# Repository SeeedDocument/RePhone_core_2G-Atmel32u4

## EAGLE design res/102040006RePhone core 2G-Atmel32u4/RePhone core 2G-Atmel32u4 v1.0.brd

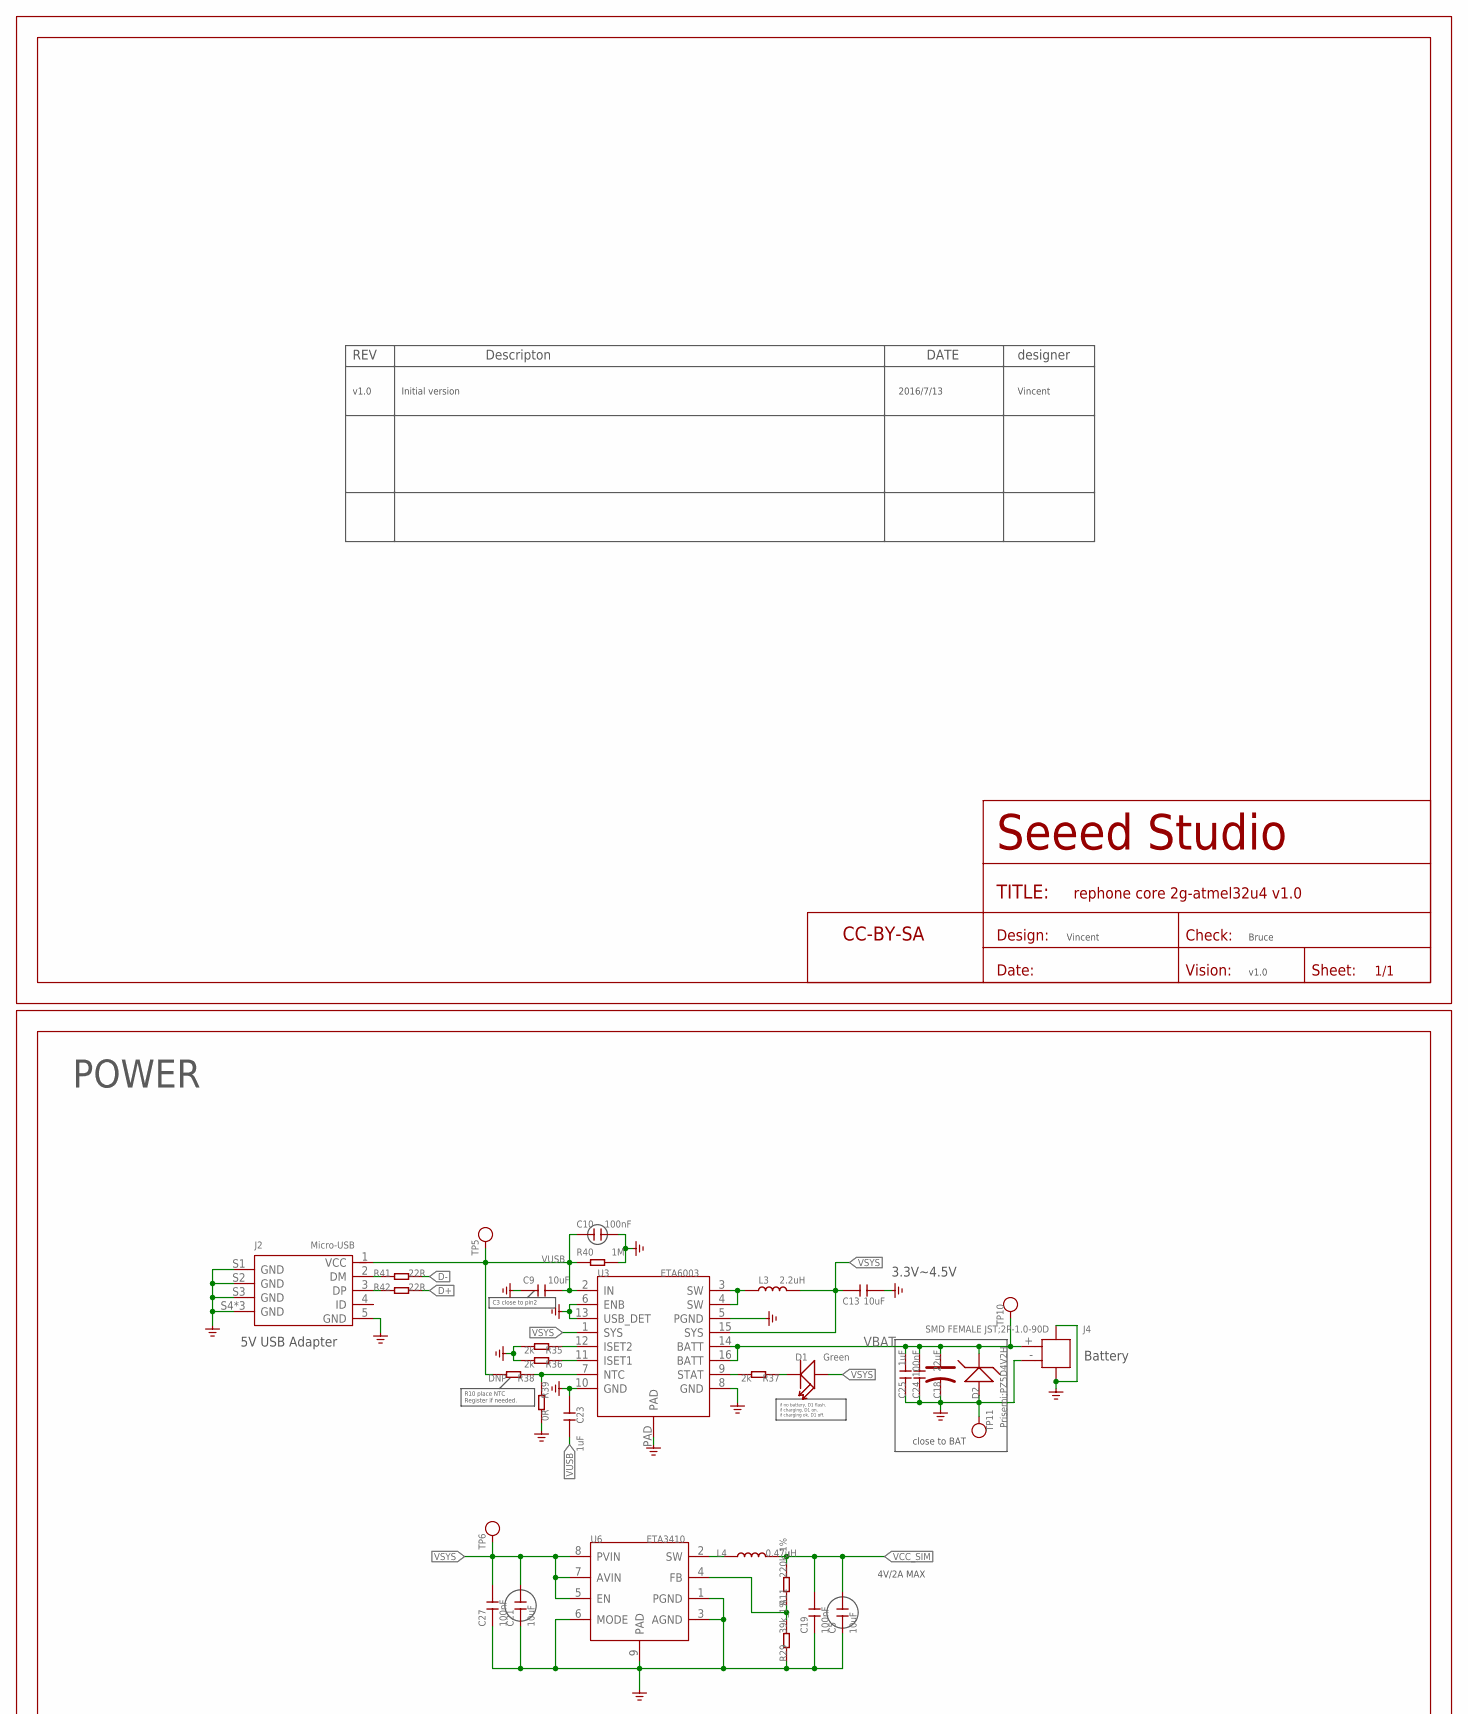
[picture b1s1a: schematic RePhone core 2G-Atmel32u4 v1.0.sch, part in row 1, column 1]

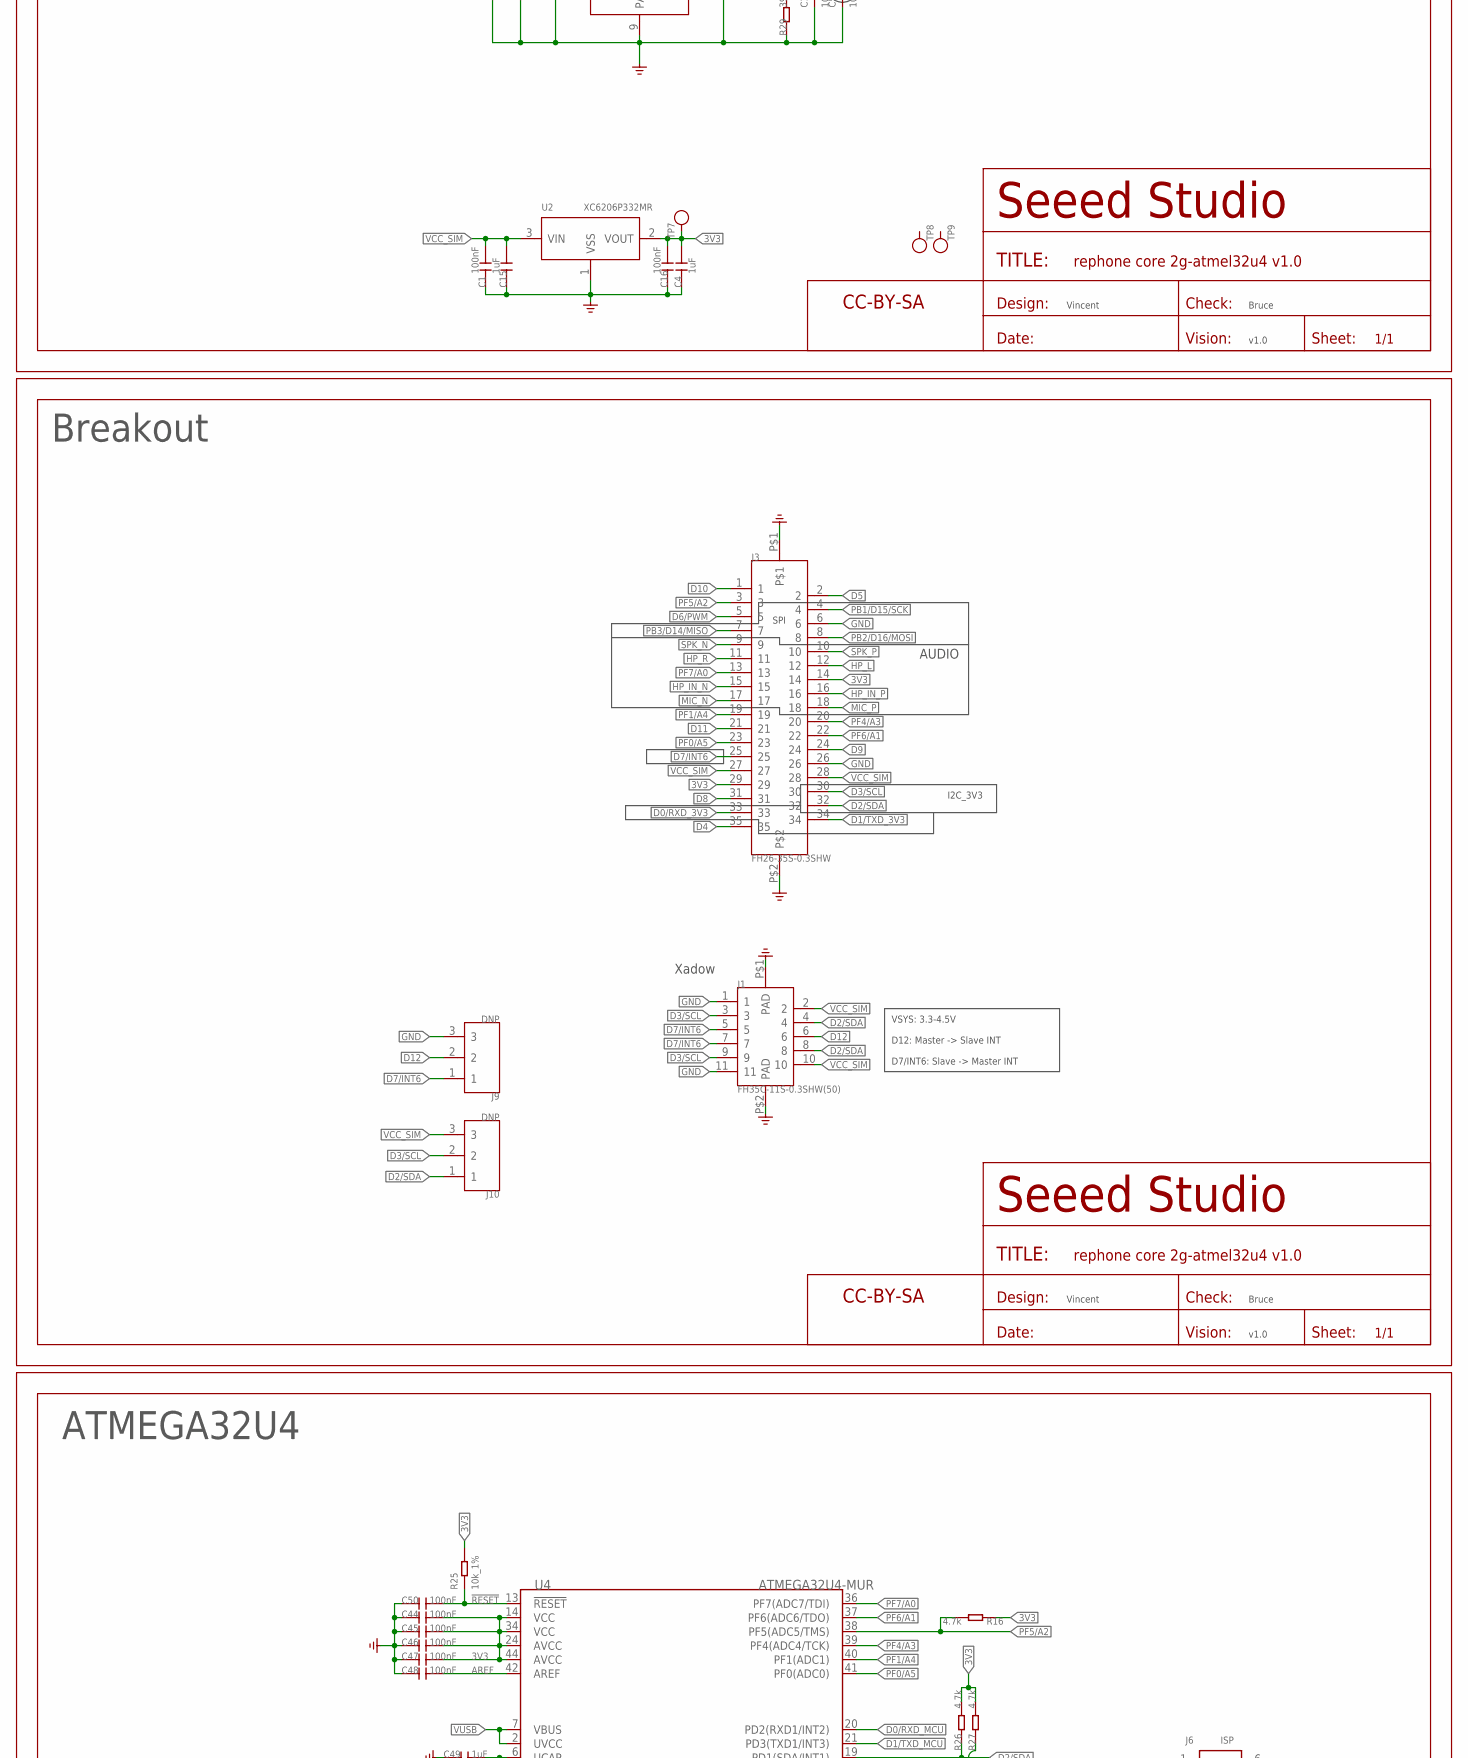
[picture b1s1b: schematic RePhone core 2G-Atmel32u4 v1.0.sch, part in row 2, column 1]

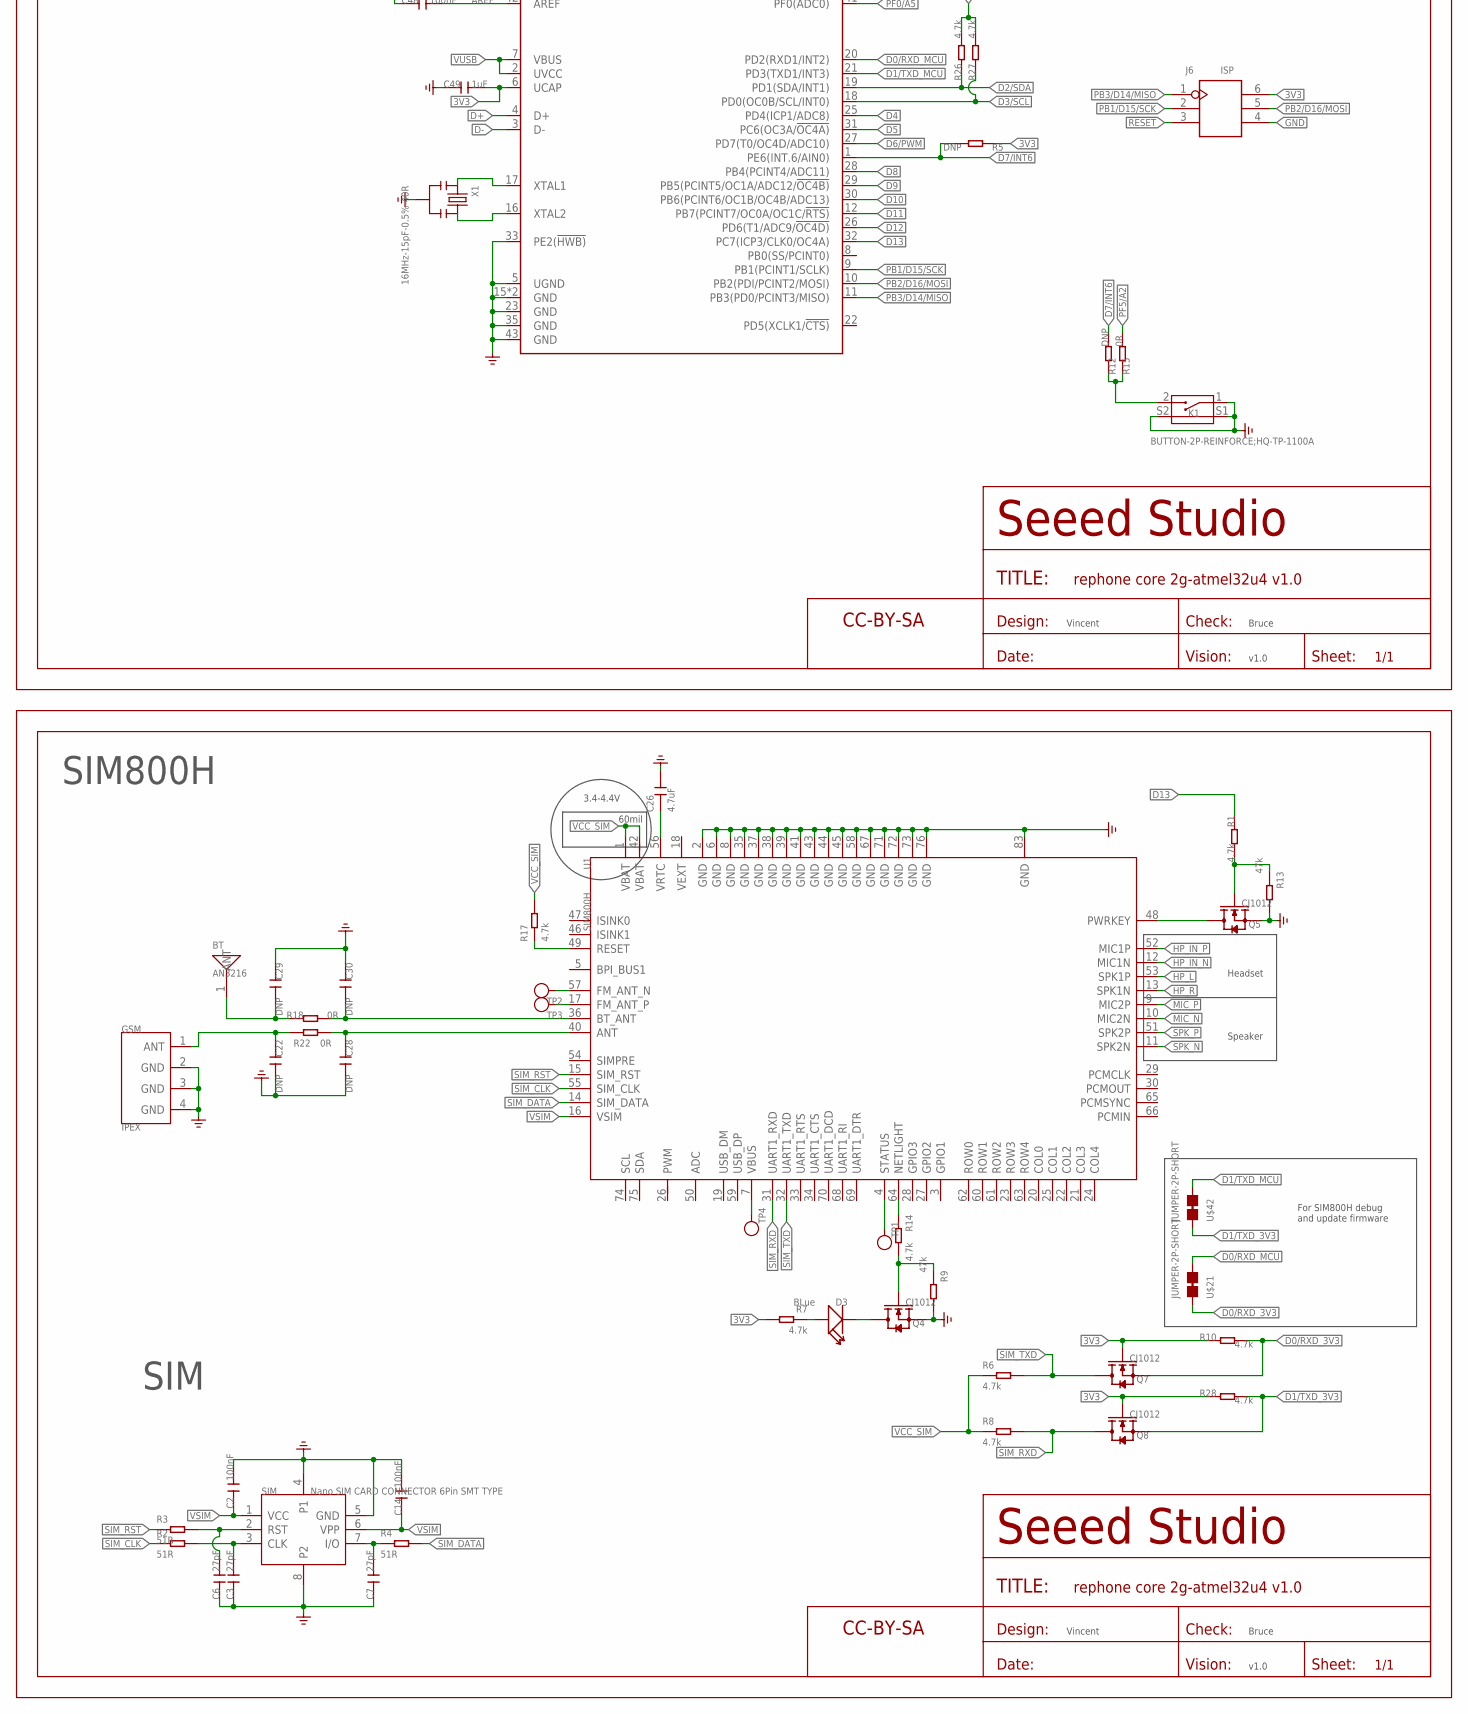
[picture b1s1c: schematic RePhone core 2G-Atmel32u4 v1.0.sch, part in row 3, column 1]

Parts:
BT: AN3216; ANT-SMD2P-3.2X1.6X1.04MM
C1, C2, C10, C14, C16, C19, C24, C27, C44, C45, C46, C47, C48, C50: 100nF; C0201
C3, C6, C7: 27pF; C0201
C4, C15, C23, C25, C49: 1uF; C0402
C5, C9, C13, C21: 10uF; C0603
C18: 22uF; AVX-A
C22, C28, C29, C30: DNP; C0201
C26: 4.7uF; C0603
D1: Green; LED-0402
D2: Prisemi;PZ5D4V2H; SOD-523
D3: BLue; LED-0402
FR1, FR2: SEEEDSTUDIO-OPEN-SCH-FRAME; SEEEDSTUDIO-PCB-FRAME
GSM: IPEX; ANT-IPEX4-1.7X1.7MM
J1: FH35C-11S-0.3SHW(50); FPC11-SMD-0.3(FH35C)
J2: Micro-USB; MICRO-USB5+4P-SMD-0.65-B
J3: FH26-35S-0.3SHW; FPC35-SMD-0.3(FH26W)
J4: SMD FEMALE JST;2P-1.0-90D; HW2-SMD-1.0-90D
J6: ISP; H2X3-SMD-2.0(1.143)
J9, J10: DNP; 3P-DIP-2
K1: BUTTON-2P-REINFORCE;HQ-TP-1100A; SW4-SMD-4.5X3.8X1.8MM-90D
L3: 2.2uH; L0805
L4: 0.47uH; L201610
Q4, Q5, Q7, Q8: CJ1012; SOT-523
R1, R6, R7, R8, R10, R14, R16, R17, R26, R27, R28: 4.7k; R0201
R2, R3, R4: 51R; R0201
R5, R12, R38: DNP; R0201
R9, R13: 47k; R0201
R11: 220k_1%; R0201
R15, R18, R22, R39: 0R; R0201
R25: 10k_1%; R0201
R29: 39k_1%; R0201
R35, R36, R37: 2k; R0201
R40: 1M; R0201
R41, R42: 22R; R0201
SIM: Nano SIM CARD CONNECTOR 6Pin SMT TYPE; NANO-SIM6+2P-SMD-12.3X10X1.5MM
TP1, TP4, TP5, TP6, TP7, TP8, TP9, TP10, TP11: TEST-POINT-23; TP-D23MIL
TP2, TP3: TEST-POINT'4545'; TP-D45MIL
U1: SIM800H; GPRS88-SMD-1.4-17.8X45.8X2.4MM
U2: XC6206P332MR; SOT-23
U3: ETA6003; QFN16GA-0.5-3X3MM
U4: ATMEGA32U4-MUR; QFN44G-0.5-7X7MM
U6: ETA3410; DFN8G-0.5-2X2MM
U$1, U$3, U$5: SEEEDSTUDIO-OPEN-SCH-FRAME; SEEEDSTUDIO-PCB-FRAME
U$21, U$42: JUMPER-2P-SHORT; 2P-SMD-SHORT
X1: 16MHz-15pF-0.5%-40R; RESONATOR3-SMD-3.6X1.3X0.8MM

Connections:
3V3: C4.2, C16.2, C44.2, C45.2, C46.2, C47.2, C49.2, J3.14, J3.29, J6.6, Q7.1 (G), Q8.1 (G), R5.1, R7.2, R10.1, R16.1, R25.2, R26.2, R27.2, R28.1, TP7.T, U2.2 (VOUT), U4.6 (UCAP), U4.14 (VCC), U4.24 (AVCC), U4.34 (VCC), U4.44 (AVCC)
!RESET: C50.2, J6.3, R25.1, U4.13 (!RESET)
AREF: C48.2, U4.42 (AREF)
D0/RXD_3V3: J3.33, Q7.2 (S), R10.2, U$21.1
D0/RXD_MCU: U4.20 (PD2(RXD1/INT2)), U$21.2
D1/TXD_3V3: J3.34, Q8.2 (S), R28.2, U$42.1
D1/TXD_MCU: U4.21 (PD3(TXD1/INT3)), U$42.2
D2/SDA: J1.4, J1.8, J3.32, J10.1, R26.1, U4.19 (PD1(SDA/INT1))
D3/SCL: J1.3, J1.9, J3.30, J10.2, R27.1, U4.18 (PD0(OC0B/SCL/INT0))
D4: J3.35, U4.25 (PD4(ICP1/ADC8))
D5: J3.2, U4.31 (PC6(OC3A/!OC4A))
D6/PWM: J3.5, U4.27 (PD7(T0/OC4D/ADC10))
D7/INT6: J1.5, J1.7, J3.25, J9.1, R5.2, R12.2, U4.1 (PE6(INT.6/AIN0))
D8: J3.31, U4.28 (PB4(PCINT4/ADC11))
D9: J3.24, U4.29 (PB5(PCINT5/OC1A/ADC12/!OC4B))
D10: J3.1, U4.30 (PB6(PCINT6/OC1B/OC4B/ADC13))
D11: J3.21, U4.12 (PB7(PCINT7/OC0A/OC1C/!RTS))
D12: J1.6, J9.2, U4.26 (PD6(T1/ADC9/!OC4D))
D13: R1.1, U4.32 (PC7(ICP3/CLK0/OC4A))
D+: R42.2, U4.4 (D+)
D-: R41.2, U4.3 (D-)
GND: C1.1, C2.2, C3.1, C4.1, C5.1, C6.1, C7.1, C9.2, C10.2, C13.2, C14.2, C15.1, C16.1, C18.-, C19.1, C21.1, C22.2, C23.2, C24.2, C25.2, C26.2, C27.1, C28.2, C29.1, C30.1, C44.1, C45.1, C46.1, C47.1, C48.1, C49.1, C50.1, D2.+, GSM.2 (GND), GSM.3 (GND), GSM.4 (GND), J1.1, J1.11, J1.P$1 (PAD), J1.P$2 (PAD), J2.5 (GND), J2.S1 (GND), J2.S2 (GND), J2.S3 (GND), J2.S4 (GND), J2.S5 (GND), J2.S6 (GND), J3.6, J3.26, J3.P$1, J3.P$2, J4.3, J4.4, J4.- (2), J6.4, J9.3, K1.1, K1.S1, K1.S2, Q4.2 (S), Q5.2 (S), R9.2, R13.2, R29.1, R35.2, R36.2, R39.2, R40.2, SIM.4 (P1), SIM.5 (GND), SIM.8 (P2), TP11.T, U1.2 (GND), U1.6 (GND), U1.8 (GND), U1.35 (GND), U1.37 (GND), U1.38 (GND), U1.39 (GND), U1.41 (GND), U1.43 (GND), U1.44 (GND), U1.45 (GND), U1.58 (GND), U1.67 (GND), U1.71 (GND), U1.72 (GND), U1.73 (GND), U1.76 (GND), U1.83 (GND), U2.1 (VSS), U3.5 (PGND), U3.6 (ENB), U3.8 (GND), U3.10 (GND), U3.13 (USB_DET), U3.PAD, U4.5 (UGND), U4.15 (GND), U4.23 (GND), U4.33 (PE2(!HWB)), U4.35 (GND), U4.43 (GND), U4.TAB (GND), U6.1 (PGND), U6.3 (AGND), U6.6 (MODE), U6.9 (PAD), X1.2
HP_IN_N: J3.15, U1.12 (MIC1N)
HP_IN_P: J3.16, U1.52 (MIC1P)
HP_L: J3.12, U1.53 (SPK1P)
HP_R: J3.11, U1.13 (SPK1N)
MIC_N: J3.17, U1.10 (MIC2N)
MIC_P: J3.18, U1.9 (MIC2P)
unnamed: L4.1, U6.2 (SW)
unnamed: U4.17 (XTAL1), X1.1
unnamed: Q5.3 (D), U1.48 (PWRKEY)
unnamed: R11.1, R29.2, U6.4 (FB)
unnamed: TP4.T, U1.7 (VBUS)
unnamed: C26.1, U1.56 (VRTC)
unnamed: TP2.T, U1.57 (FM_ANT_N)
unnamed: TP3.T, U1.17 (FM_ANT_P)
unnamed: C3.2, R2.2, SIM.3 (CLK)
unnamed: C6.2, R3.2, SIM.2 (RST)
unnamed: Q4.1 (G), R9.1, R14.2
unnamed: R35.1, U3.12 (ISET2)
unnamed: D3.+, R7.1
unnamed: D3.-, Q4.3 (D)
unnamed: R36.1, U3.11 (ISET1)
unnamed: L3.1, U3.3 (SW), U3.4 (SW)
unnamed: R37.2, U3.9 (STAT)
unnamed: D1.-, R37.1
unnamed: R38.1, R39.1, U3.7 (NTC)
unnamed: R14.1, U1.64 (NETLIGHT)
unnamed: R17.1, U1.49 (RESET)
unnamed: Q5.1 (G), R1.2, R13.1
unnamed: J2.2 (DM), R41.1
unnamed: J2.3 (DP), R42.1
unnamed: U4.16 (XTAL2), X1.3
unnamed: TP1.T, U1.4 (STATUS)
unnamed: BT.1, C29.2, R18.2
unnamed: C22.1, GSM.1 (ANT), R22.2
unnamed: C28.1, R22.1, U1.40 (ANT)
unnamed: C30.2, R18.1, U1.36 (BT_ANT)
unnamed: C7.2, R4.1, SIM.7 (I/O)
unnamed: K1.2, R12.1, R15.1
PB1/D15/SCK: J3.4, J6.2, U4.9 (PB1(PCINT1/SCLK))
PB2/D16/MOSI: J3.8, J6.5, U4.10 (PB2(PDI/PCINT2/MOSI))
PB3/D14/MISO: J3.7, J6.1, U4.11 (PB3(PD0/PCINT3/MISO))
PF0/A5: J3.23, U4.41 (PF0(ADC0))
PF1/A4: J3.19, U4.40 (PF1(ADC1))
PF4/A3: J3.20, U4.39 (PF4(ADC4/TCK))
PF5/A2: J3.3, R15.2, R16.2, U4.38 (PF5(ADC5/TMS))
PF6/A1: J3.22, U4.37 (PF6(ADC6/TDO))
PF7/A0: J3.13, U4.36 (PF7(ADC7/TDI))
SIM_CLK: R2.1, U1.55 (SIM_CLK)
SIM_DATA: R4.2, U1.14 (SIM_DATA)
SIM_RST: R3.1, U1.15 (SIM_RST)
SIM_RXD: Q8.3 (D), R8.2, U1.31 (UART1_RXD)
SIM_TXD: Q7.3 (D), R6.2, U1.32 (UART1_TXD)
SPK_N: J3.9, U1.11 (SPK2N)
SPK_P: J3.10, U1.51 (SPK2P)
VBAT: C18.+, C24.1, C25.1, D2.-, J4.+ (1), TP10.T, U3.14 (BATT), U3.16 (BATT)
VCC_SIM: C1.2, C5.2, C15.2, C19.2, J1.2, J1.10, J3.27, J3.28, J10.3, L4.2, R6.1, R8.1, R11.2, R17.2, U1.1 (VBAT), U1.42 (VBAT), U2.3 (VIN)
VSIM: C2.1, C14.1, SIM.1 (VCC), SIM.6 (VPP), U1.16 (VSIM)
VSYS: C13.1, C21.2, C27.2, D1.+, L3.2, TP6.T, U3.1 (SYS), U3.15 (SYS), U6.5 (EN), U6.7 (AVIN), U6.8 (PVIN)
VUSB: C9.1, C10.1, C23.1, J2.1 (VCC), R38.2, R40.1, TP5.T, U3.2 (IN), U4.2 (UVCC), U4.7 (VBUS)

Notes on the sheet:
Breakout
Xadow
POWER
SIM
AUDIO
I2C_3V3
SPI
Vincent
Bruce
v1.0
REV
Descripton
DATE
designer
R10 place NTC Register if needed.
C3 close to pin2
if no battery, D1 flash. if charging, D1 on. if charging ok, D1 off.
Battery
5V USB Adapter
3.3V~4.5V
close to BAT
ATMEGA32U4
60mil
SIM800H
D7/INT6: Slave -> Master INT
D12: Master -> Slave INT
VSYS: 3.3-4.5V
3.4-4.4V
4V/2A MAX
For SIM800H debug and update firmware
Speaker
Headset
Initial version
2016/7/13

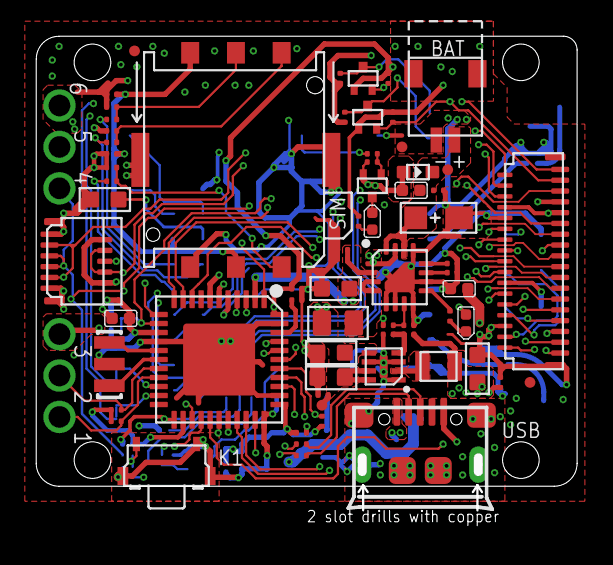
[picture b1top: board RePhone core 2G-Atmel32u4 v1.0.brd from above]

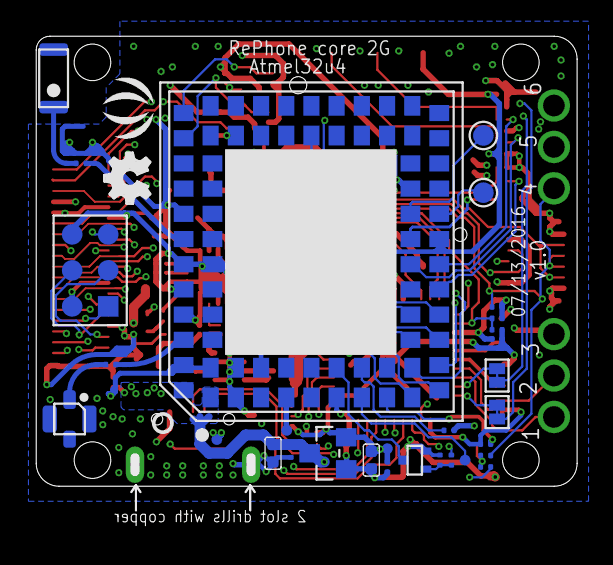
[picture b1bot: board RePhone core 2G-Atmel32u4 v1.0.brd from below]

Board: 4 copper layers, 30.0 x 26.3 mm, 110 parts (36 on the bottom side), 81 nets.

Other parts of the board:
U$2: SEEED-SILK-160*153MIL
U$14: OSHW_FILLX100_NOTEXT

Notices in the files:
parts and their libraries:
moudle-new: This work is licensed under the Creative Commons Attribution 4.0 International License.
To view a copy of this license,visit:
http://creativecommons.org/licenses/by-sa/4.0
moudle-new: CC-BY-SA
